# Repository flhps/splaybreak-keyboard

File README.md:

# SplayBreak

_A simple but versatile 36-key split ergonomic wireless keyboard._

---

_Model B with MX switches and XDA keycaps_

_Model A with MX switches and OEM keycaps_

This is a split keyboard, that is heavily inspired by my recent personal dive into the world of open mechanical split keyboards. At the time of writing, I have used these two models on an almost daily basis for over 6 months.

## Features

There are two models that use the same PCB and mostly the same build parts:

| Model                  | Hot Swap MX | Hot Swap Choc V1 | Gasket Mount | Battery | Magnetic Access Hatch | Nice Buttons and Port |
| ---------------------- | ----------- | ---------------- | ------------ | ------- | --------------------- | ----------------- |
| [A](/build-guide-a.md) | ✅          | ⚠               | ✅           | 2000mAh | ✅                    |                   |
| [B](/build-guide-b.md) | ✅          | ⚠               |              | 500mAh  |                       | ✅                |

More information can be found in the individual build guides:

- [SplayBreak Model A](/build-guide-a.md)
- [SplayBreak Model B](/build-guide-b.md)

> [!WARNING]
> While the PCB accepts hot swap sockets for Choc V1 switches, the case dimensions are not tested with them.

## Design Rationale

A big focus was to keep this keyboard somewhat simple and cheap. That is why it uses the popular Pro Micro controllers and that limits the number of keys per side to 18 because we want to avoid having to solder diodes. The keyboards are wireless with massive batteries for easier daily use at home and on the go. Since the whole keyboard layout is in the firmware, these can also be used with devices such as phones or tablets. While screens can be cool, this design has none because they cost money and reduce battery life.

For flexibility (and cost reduction), the PCB is reversible. It means you need to order less and any PCB you have left can replace one that you accidentally destroyed. Also, the PCB has support for MX switches and Choc v1 switches. That would enable the use of this PCB for a super thin travel option.

There are only two thumb keys, because they would increase the design's footprint by a lot if they were to be positioned comfortably. The current inner thumb key is the resting position, meaning a third one would have to be even more toward the inside. However, I wanted to create a somewhat compact key arrangement and case.
Instead, the extra thumb key is moved to the pinky. This emulates the extra outer keys like tab or enter on a conventional keyboard an is intended to make it easier for people who frequently switch between conventional and split keyboards. It also makes switching from a conventional keyboard to this one easier.

This project features two different keyboard models, which only differ in assembly instructions and the provided case files, which are FDM-printable. I was never a big fan of the very gritty designs featuring lots of open electronics, so I designed some fully enclosed cases.

For repairability, model A has everything socketed, making error search and replacements easier. It is also built to improve sound through a gasket mount. Model B foregoes some of that and becomes more compact and arguably more stylish. There, the controller is soldered directly to the PCB.

## Firmware and Layout

Both models can use the same firmware. I have prepared a template that already contain a usable layout:

[zmk-config-splaybreak-template](https://github.com/flhps/zmk-config-splaybreak-template)

## Open Ideas and TODOs

- clean up the PCB and make it more aesthetic (transparent case?)
- create another model as a thin travel option with choc v1
- more in-depth build guides

## Development

Build ergogen in the `ergogen` directory:

```sh
ergogen --clean .
```

## Attributions

Big inspirations were:

- [TOTEM](https://github.com/GEIGEIGEIST/TOTEM)
- [Ferris Sweep](https://github.com/davidphilipbarr/Sweep)

The design uses ergogen footprints from [@ceoloide's ergogen PCB footprints](https://github.com/ceoloide/ergogen-footprints).
The reversible hotswap footprint for both MX and Choc is extracted from the [Lily58 Pro's](https://github.com/kata0510/Lily58) kicad file.

The [ergogen guide](https://flatfootfox.com/ergogen-introduction/) from FlatFootFox was very helpful.

And of course, this project would probably not exist without the excellent tool that is [ergogen](https://github.com/ergogen/ergogen).

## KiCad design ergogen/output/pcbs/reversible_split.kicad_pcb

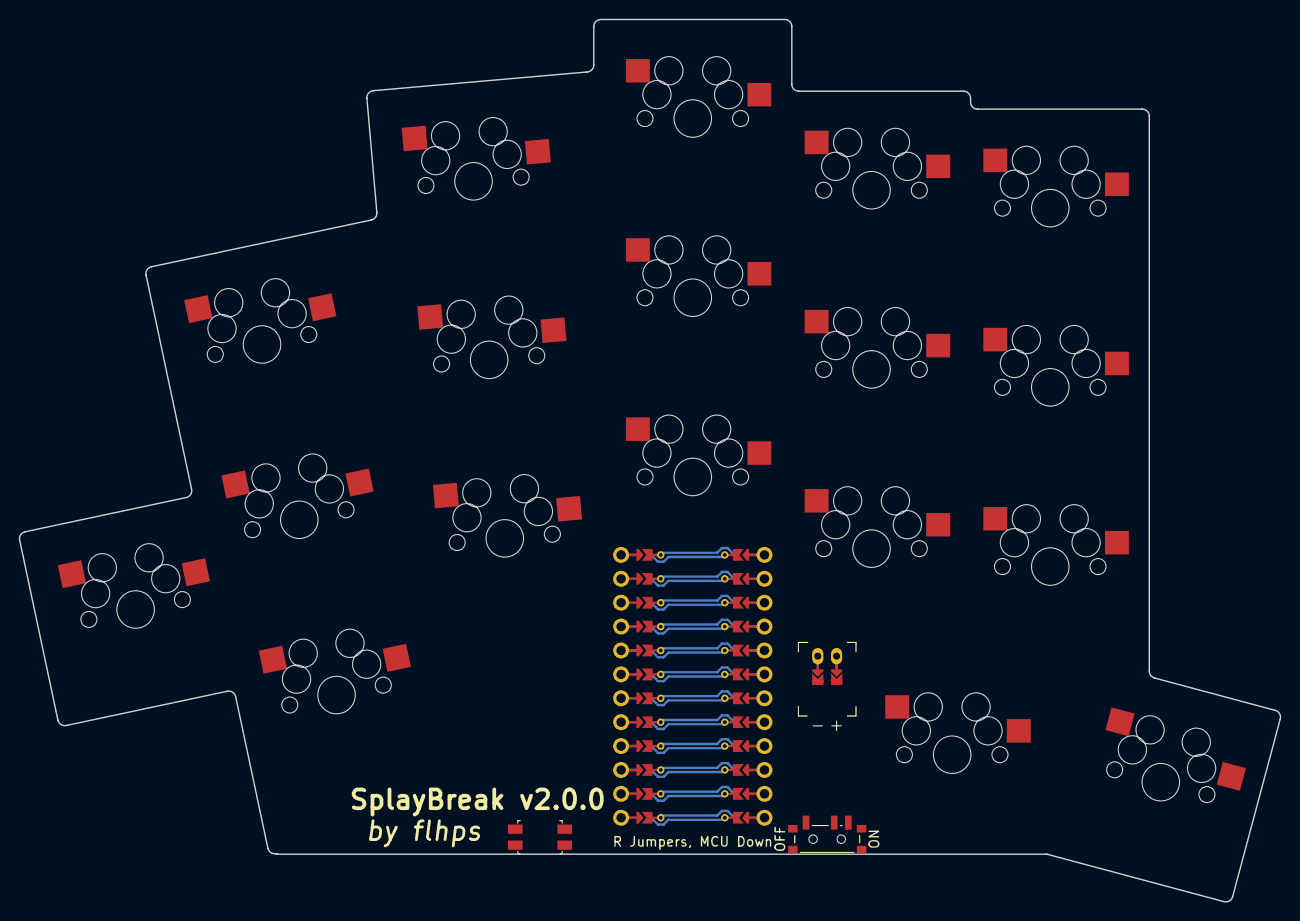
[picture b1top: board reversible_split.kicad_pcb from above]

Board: 2 copper layers, 134.0 x 93.8 mm, 22 parts (0 on the bottom side), 24 nets.

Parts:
JST1: battery_connector_jst_ph_2
MCU1: mcu_nice_nano
PWR1: power_switch_smd_side
RST1: reset_switch_smd_side
S1, S2, S3, S4, S5, S6, S7, S8, S9, S10, S11, S12, S13, S14, S15, S16, S17, S18: MX

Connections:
GND: JST1.2, MCU1.103, MCU1.104, MCU1.123, RST1.1, RST1.3, S1.1, S2.1, S3.1, S4.1, S5.1, S6.1, S7.1, S8.1, S9.1, S10.1, S11.1, S12.1, S13.1, S14.1, S15.1, S16.1, S17.1, S18.1
JST1_1: JST1.11, JST1.21, JST1.31
JST1_2: JST1.12, JST1.22, JST1.32
RAW: MCU1.124, PWR1.2
RST: MCU1.122, RST1.2, RST1.4
matrix_index_bottom: MCU1.107, S11.2
matrix_index_home: MCU1.108, S12.2
matrix_index_top: MCU1.109, S13.2
matrix_inner_bottom: MCU1.110, S14.2
matrix_inner_home: MCU1.111, S15.2
matrix_inner_top: MCU1.112, S16.2
matrix_middle_bottom: MCU1.102, S8.2
matrix_middle_home: MCU1.105, S9.2
matrix_middle_top: MCU1.106, S10.2
matrix_outer_home: MCU1.115, S1.2
matrix_pinky_bottom: MCU1.116, S2.2
matrix_pinky_home: MCU1.117, S3.2
matrix_pinky_top: MCU1.118, S4.2
matrix_ring_bottom: MCU1.119, S5.2
matrix_ring_home: MCU1.120, S6.2
matrix_ring_top: MCU1.101, S7.2
pos: JST1.1, PWR1.1, PWR1.3
thumb_reachy: MCU1.113, S18.2
thumb_tucky: MCU1.114, S17.2

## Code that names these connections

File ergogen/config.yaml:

# `U` is a predefined unit of measure that means 19.05mm, which is MX spacing
meta:
  engine: 4.1.0
units:
  pu: U + 2
points:
  zones:
    matrix:
      columns:
        outer:
          rows.bottom.skip: true
          rows.top.skip: true
        pinky.key.stagger: 0.3U
        ring.key:
          stagger: 0.66U
          splay: -7
          spread: 1.1U
        middle.key:
          stagger: 0.25U
          splay: -5
          spread: 1.075U
        index.key.stagger: -0.4U
        inner.key.stagger: -0.1U
      rows:
        bottom.padding: U
        home.padding: U
        top.padding: U
      rotate: 12
      anchor:
        # Shift the PCB slightly to the right and down, otherwise it's weirdly positioned outside of the main sheet in KiCad
        shift: [100, -150]
    thumb:
      anchor:
        ref: matrix_index_bottom
        shift: [0.45U, -1.15U]
      columns:
        tucky:
          key.name: thumb_tucky
          key.splay: 0
        reachy:
          key.spread: 1U
          key.splay: -15
          key.origin: [-0.5U, -0.7U]
          key.name: thumb_reachy
outlines:
  keys:
    - what: rectangle
      where: true
      size: [1U, 1U]
  raw:
    - what: rectangle
      where: true
      size: [1pu, 1pu]
  pinky_right:
    - what: rectangle
      where:
        - ref: matrix_pinky_top
          shift: [1.0U, -0.5pu]
      size: [1pu, 2pu]
  ring_right:
    - what: rectangle
      where:
        - ref: matrix_ring_top
          shift: [1.0U, -0.5pu]
      size: [1pu, 2pu]
  thumb_up:
    - what: rectangle
      where:
        - ref: thumb_tucky
          shift: [0U, 1U]
      size: [1pu, 1pu]
  inner_down:
    - what: rectangle
      where:
        - ref: matrix_inner_bottom
          shift: [0U, -0.9U]
      size: [1pu, 1pu]
  combined_raw:
    - name: raw
    - operation: add
      name: pinky_right
    - operation: add
      name: ring_right
    - operation: add
      name: thumb_up
    - operation: add
      name: inner_down
  io_rect:
    - what: rectangle
      where:
        - ref: matrix_middle_bottom
          shift: [0pu, -1U]
          rotate: 0
      size: [4.2pu, 2pu]
  io_fill:
    - what: rectangle
      where:
        - ref: matrix_pinky_bottom
          shift: [0pu, -1U]
          rotate: 0
      size: [1pu, 1pu]
  io_fill2:
    - what: rectangle
      where:
        - ref: thumb_tucky
          shift: [-4pu, 0U]
          rotate: 0
      size: [8pu, 1pu]
  io_patch:
    - name: io_fill
    - operation: intersect
      name: io_fill2
  board:
    - name: combined_raw
    - operation: add
      name: io_rect
    - operation: add
      name: io_patch
      fillet: 0.75
pcbs:
  reversible_split:
    template: kicad8
    outlines:
      main:
        outline: board
    footprints:
      keys:
        what: mx
        where: true
        params:
          from: GND
          to: "{{name}}"
          reverse: true
          keycaps: true
          hotswap: true
      mcu:
        what: mcu_nice_nano
        where:
          - ref: matrix_middle_bottom
            shift: [0U, -1.235U]
            rotate: 180
        params:
          reversible: true
          reverse_mount: true
          show_silk_labels: false
          show_via_labels: false
          # right side pins
          P21: matrix_ring_home
          P20: matrix_ring_bottom
          P19: matrix_pinky_top
          P18: matrix_pinky_home
          P15: matrix_pinky_bottom
          P14: matrix_outer_home
          P16: thumb_tucky
          P10: thumb_reachy
          # left side pins
          P1: matrix_ring_top
          P0: matrix_middle_bottom
          P2: matrix_middle_home
          P3: matrix_middle_top
          P4: matrix_index_bottom
          P5: matrix_index_home
          P6: matrix_index_top
          P7: matrix_inner_bottom
          P8: matrix_inner_home
          P9: matrix_inner_top
      battery_connector:
        what: battery_connector_jst_ph_2
        where:
          ref:
            - matrix_middle_bottom
          shift: [0.75U, -1U]
          rotate: 0
        params:
          reversible: true
          BAT_N: GND
          BAT_P: pos
      on_off_switch:
        what: power_switch_smd_side
        where:
          ref:
            - matrix_middle_bottom
          shift: [0.75U, -2.02U]
          rotate: -90
        params:
          reversible: true
          from: pos
          to: RAW
      horizontal_reset:
        what: reset_switch_smd_side
        where:
          ref:
            - thumb_tucky
          shift: [-2.3U, -0.46U]
          rotate: -180
        params:
          reversible: true
          from: GND
          to: RST
      version_text:
        what: utility_text
        where:
          - ref: matrix_middle_bottom
            shift: [-1.2U, -1.8U]
        params:
          reversible: true
          height: 2
          width: 2
          thickness: 0.4
          text: "SplayBreak v2.0.0"
      author_text:
        what: utility_text
        where:
          - ref: matrix_middle_bottom
            shift: [-1.5U, -1.975U]
        params:
          reversible: true
          height: 2
          width: 2
          thickness: 0.3
          italic: true
          text: "by flhps"

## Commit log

2024-08-31 Initial Design
2024-08-31 Tighter outline
2024-09-01 First complete layout
2024-09-01 Rotated layout experiment
2024-09-03 Updated SMD positions
2024-10-06 First Complete PCB
2024-11-24 New ergogen config finalized
2024-11-24 Replaced mx footprint with hybrid footprint
2024-11-27 Manually flipped mc footprint
    The ergogen footprint for the mcu seems buggy.
2024-11-27 Routed quick and dirty
2024-11-28 Final production files
2025-04-02 Iteration One (#1)
    * Tighter outline
    * First complete layout
    * Rotated layout experiment
    * Updated SMD positions
    * First Complete PCB
2025-04-02 Reverted name change
2025-06-12 Write most of README
2025-06-12 Wrote build guide b
2025-06-12 Finished build guides
2025-06-13 Added case step files
2025-06-13 Improved instructions
2025-06-13 Regenerated build files with updated text
2025-06-13 Create LICENSE
